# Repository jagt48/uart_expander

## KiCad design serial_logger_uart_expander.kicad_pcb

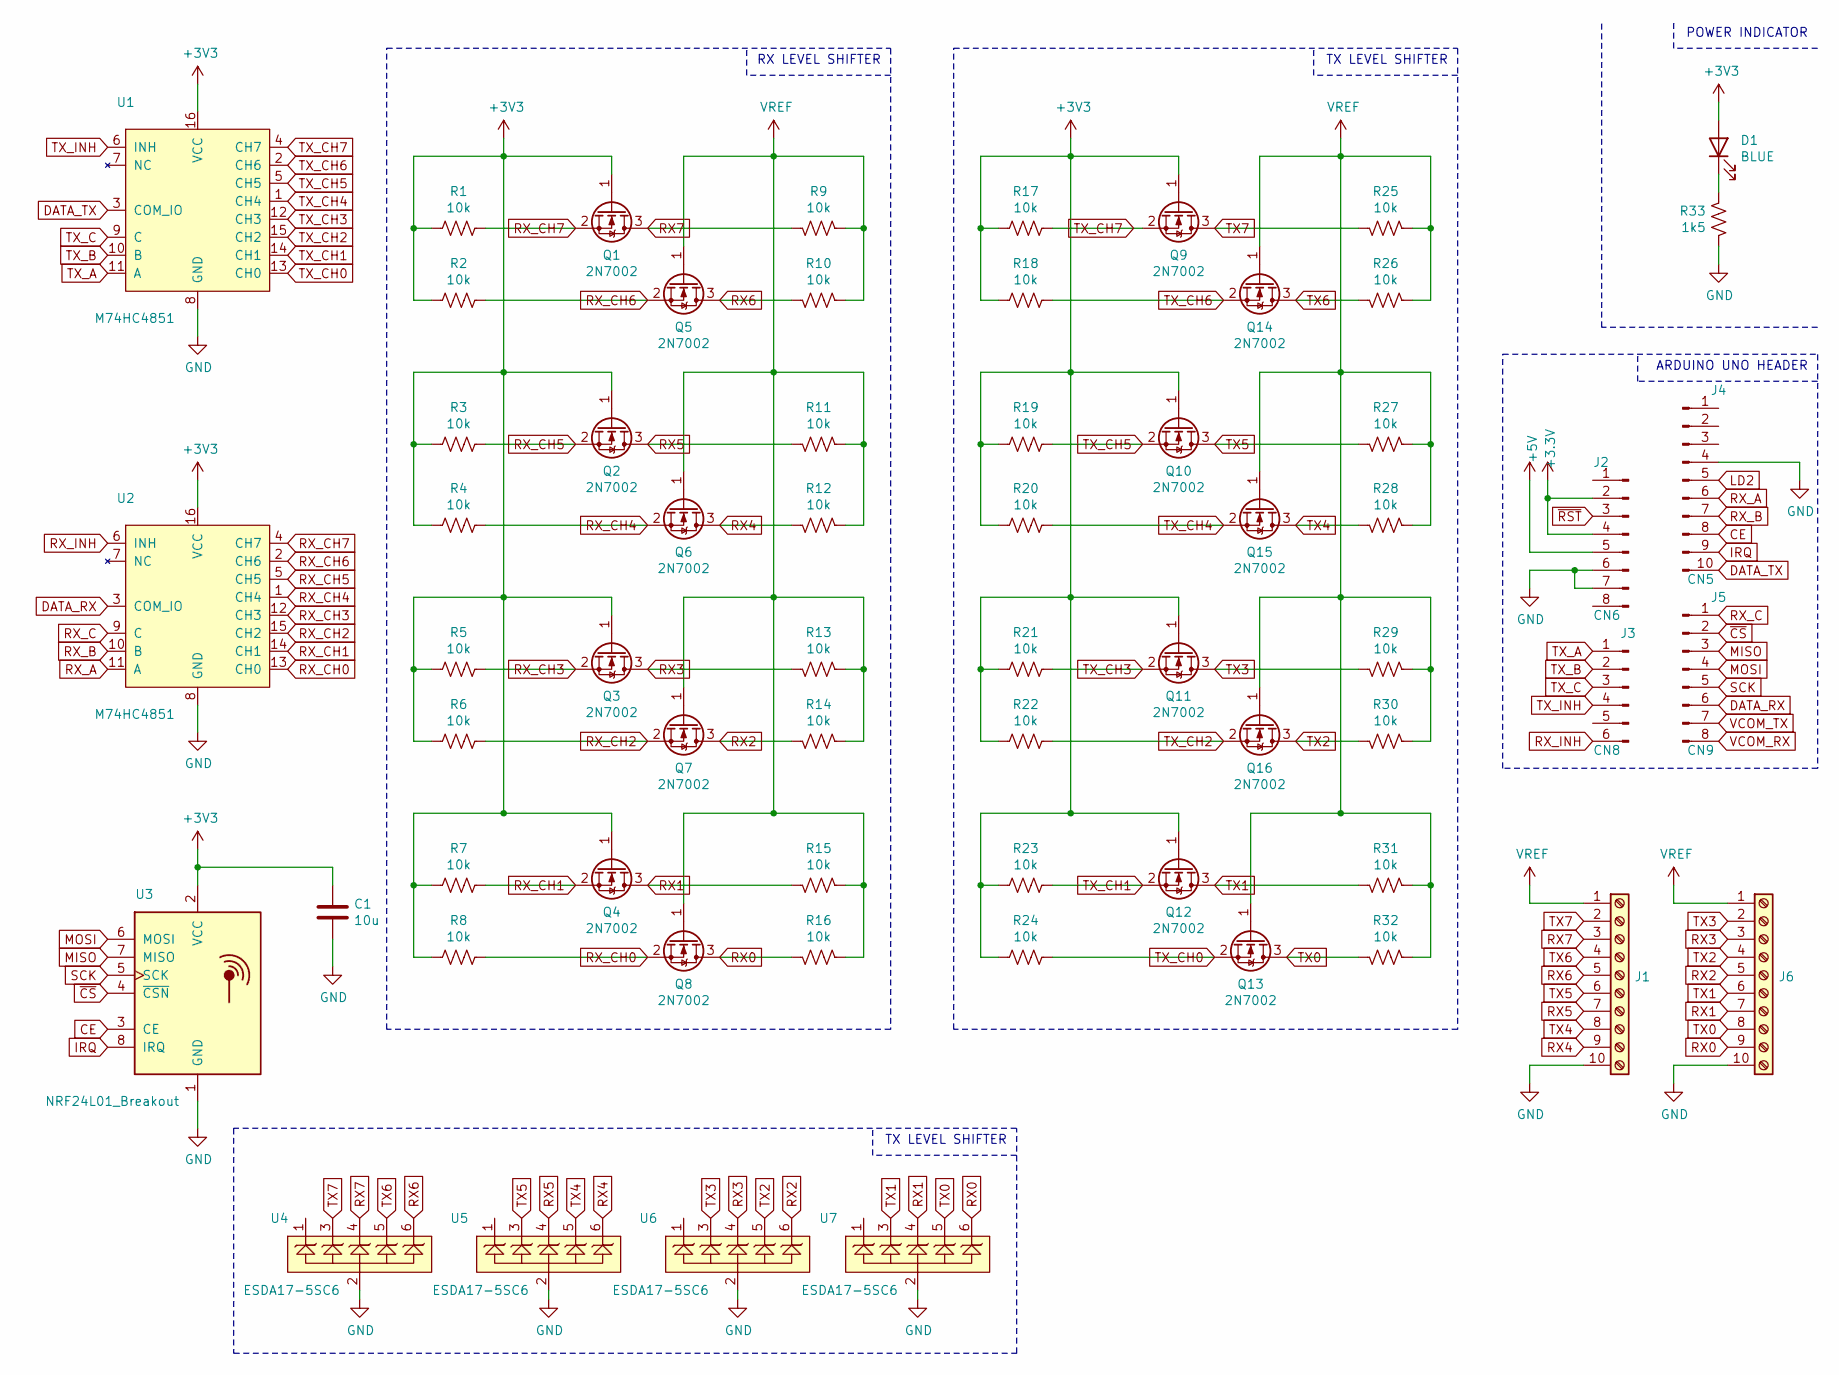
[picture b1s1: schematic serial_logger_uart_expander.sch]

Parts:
C1: 10u; C_0805_2012Metric; LCSC Part # C15850
D1: BLUE; LED_0603_1608Metric_Castellated; LCSC Part # C72041
J1, J6: Screw_Terminal_01x10; TerminalBlock_TE_1-282834-0_1x10_P2.54mm_Horizontal
J2: CN6; PinHeader_1x08_P2.54mm_Vertical
J3: CN8; PinHeader_1x06_P2.54mm_Vertical
J4: CN5; PinHeader_1x10_P2.54mm_Vertical
J5: CN9; PinHeader_1x08_P2.54mm_Vertical
Q1, Q2, Q3, Q4, Q5, Q6, Q7, Q8, Q9, Q10, Q11, Q12, Q13, Q14, Q15, Q16: 2N7002; SOT-23
R1, R2, R3, R4, R5, R6, R7, R8, R9, R10, R11, R12, R13, R14, R15, R16, R17, R18, R19, R20, R21, R22, R23, R24, R25, R26, R27, R28, R29, R30, R31, R32: 10k; R_0603_1608Metric; LCSC Part # C25804
R33: 1k5; R_0603_1608Metric; LCSC Part # C22843
U1, U2: M74HC4851; M74HC4851_ST_TSSOP-16
U3: NRF24L01_Breakout; nRF24L01_Breakout
U4, U5, U6, U7: ESDA17-5SC6; ESDA17-5SC6_SOT23-6L

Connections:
+5V: J2.5
CE: J4.8, U3.3 (CE)
DATA_RX: J5.6, U2.3 (COM_IO)
DATA_TX: J4.10, U1.3 (COM_IO)
GND: C1.2, J1.10, J2.6, J2.7, J4.4, J6.10, R33.1, U1.8 (GND), U2.8 (GND), U3.1 (GND), U4.2, U5.2, U6.2, U7.2
IRQ: J4.9, U3.8 (IRQ)
LD2: J4.5
MISO: J5.3, U3.7 (MISO)
MOSI: J5.4, U3.6 (MOSI)
unnamed: D1.1 (K), R33.2
RX0: J6.9, Q8.3 (D), R16.2, U7.6
RX1: J6.7, Q4.3 (D), R15.2, U7.4
RX2: J6.5, Q7.3 (D), R14.2, U6.6
RX3: J6.3, Q3.3 (D), R13.2, U6.4
RX4: J1.9, Q6.3 (D), R12.2, U5.6
RX5: J1.7, Q2.3 (D), R11.2, U5.4
RX6: J1.5, Q5.3 (D), R10.2, U4.6
RX7: J1.3, Q1.3 (D), R9.2, U4.4
RX_A: J4.6, U2.11 (A)
RX_B: J4.7, U2.10 (B)
RX_C: J5.1, U2.9 (C)
RX_CH0: Q8.2 (S), R8.1, U2.13 (CH0)
RX_CH1: Q4.2 (S), R7.1, U2.14 (CH1)
RX_CH2: Q7.2 (S), R6.1, U2.15 (CH2)
RX_CH3: Q3.2 (S), R5.1, U2.12 (CH3)
RX_CH4: Q6.2 (S), R4.1, U2.1 (CH4)
RX_CH5: Q2.2 (S), R3.1, U2.5 (CH5)
RX_CH6: Q5.2 (S), R2.1, U2.2 (CH6)
RX_CH7: Q1.2 (S), R1.1, U2.4 (CH7)
RX_INH: J3.6, U2.6 (INH)
SCK: J5.5, U3.5 (SCK)
TX0: J6.8, Q13.3 (D), R32.2, U7.5
TX1: J6.6, Q12.3 (D), R31.2, U7.3
TX2: J6.4, Q16.3 (D), R30.2, U6.5
TX3: J6.2, Q11.3 (D), R29.2, U6.3
TX4: J1.8, Q15.3 (D), R28.2, U5.5
TX5: J1.6, Q10.3 (D), R27.2, U5.3
TX6: J1.4, Q14.3 (D), R26.2, U4.5
TX7: J1.2, Q9.3 (D), R25.2, U4.3
TX_A: J3.1, U1.11 (A)
TX_B: J3.2, U1.10 (B)
TX_C: J3.3, U1.9 (C)
TX_CH0: Q13.2 (S), R24.1, U1.13 (CH0)
TX_CH1: Q12.2 (S), R23.1, U1.14 (CH1)
TX_CH2: Q16.2 (S), R22.1, U1.15 (CH2)
TX_CH3: Q11.2 (S), R21.1, U1.12 (CH3)
TX_CH4: Q15.2 (S), R20.1, U1.1 (CH4)
TX_CH5: Q10.2 (S), R19.1, U1.5 (CH5)
TX_CH6: Q14.2 (S), R18.1, U1.2 (CH6)
TX_CH7: Q9.2 (S), R17.1, U1.4 (CH7)
TX_INH: J3.4, U1.6 (INH)
VBUS: J1.1, J6.1, Q5.1 (G), Q6.1 (G), Q7.1 (G), Q8.1 (G), Q13.1 (G), Q14.1 (G), Q15.1 (G), Q16.1 (G), R9.1, R10.1, R11.1, R12.1, R13.1, R14.1, R15.1, R16.1, R25.1, R26.1, R27.1, R28.1, R29.1, R30.1, R31.1, R32.1
VCOM_RX: J5.8
VCOM_TX: J5.7
~CS: J5.2, U3.4 (~CSN)
~RST: J2.3

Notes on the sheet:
POWER INDICATOR
ARDUINO UNO HEADER
TX LEVEL SHIFTER
RX LEVEL SHIFTER

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
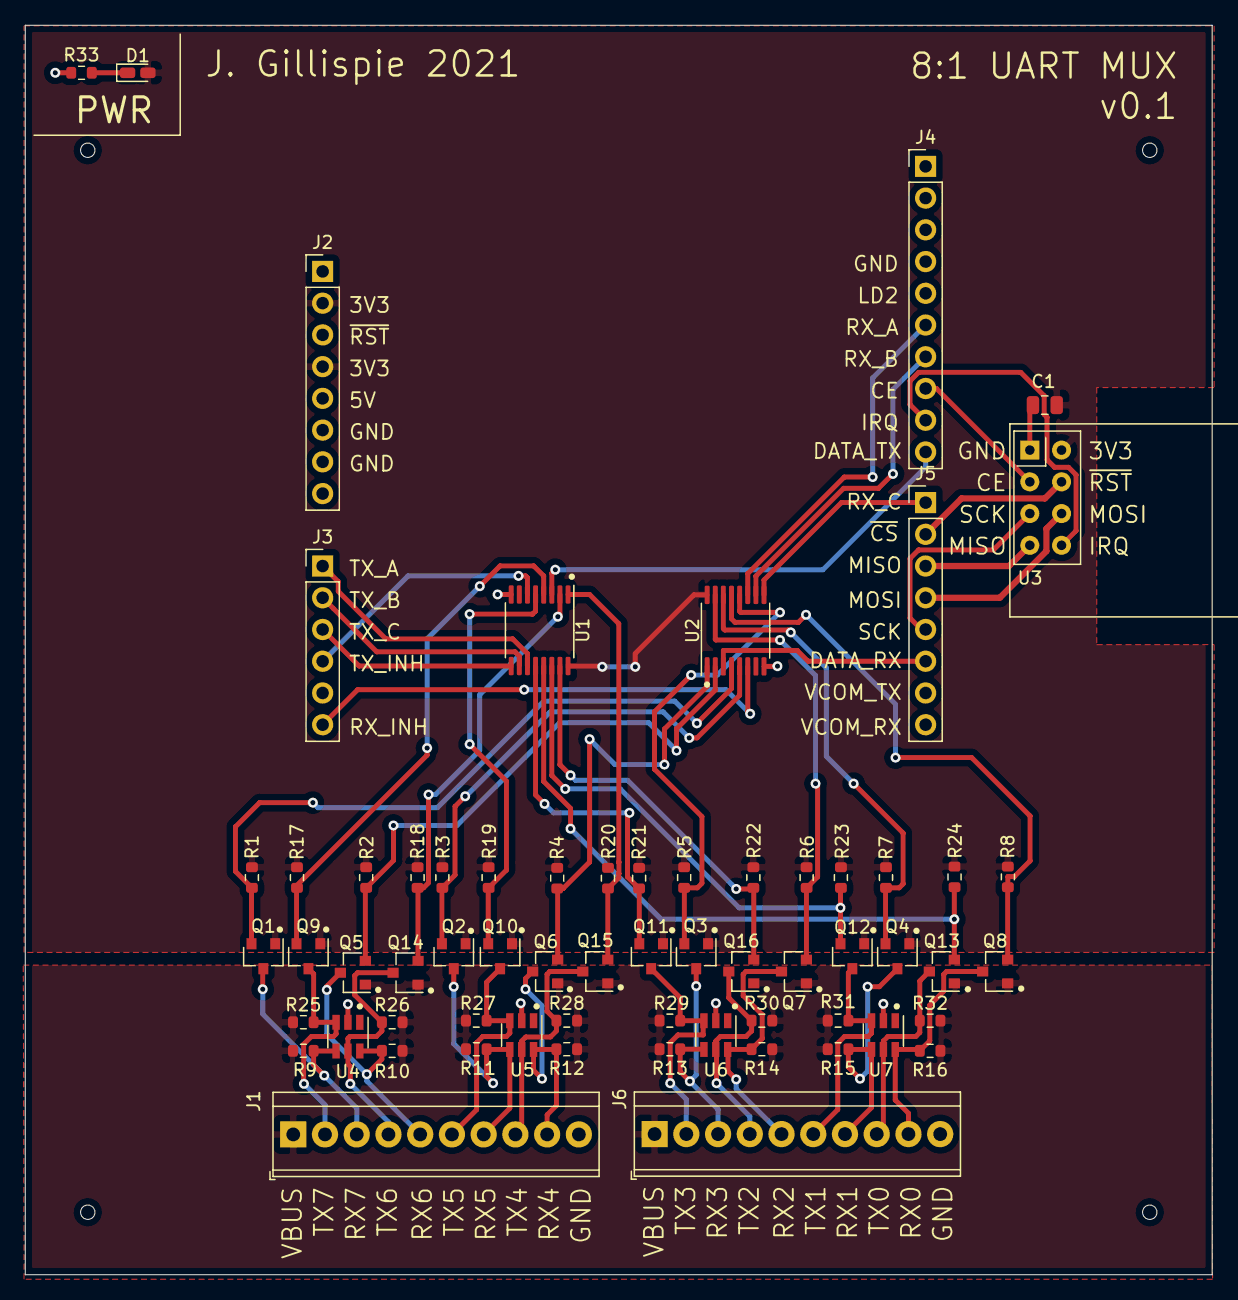
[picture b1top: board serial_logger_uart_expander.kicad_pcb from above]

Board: 2 copper layers, 95.0 x 100.0 mm, 64 parts (0 on the bottom side), 52 nets.

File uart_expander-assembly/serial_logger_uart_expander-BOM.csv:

Designator,Quantity,Value,Footprint,LCSC Part Number
"C1, ",1,10u,0805,C15850
"D1, ",1,BLUE,0603,C72041
"J1, J6, ",2,Screw_Terminal_01x10,TerminalBlock_TE-Connectivity:TerminalBlock_TE_1-282834-0_1x10_P2.54mm_Horizontal,
"J2, ",1,CN6,Connector_PinHeader_2.54mm:PinHeader_1x08_P2.54mm_Vertical,
"J3, ",1,CN8,Connector_PinHeader_2.54mm:PinHeader_1x06_P2.54mm_Vertical,
"J4, ",1,CN5,Connector_PinHeader_2.54mm:PinHeader_1x10_P2.54mm_Vertical,
"J5, ",1,CN9,Connector_PinHeader_2.54mm:PinHeader_1x08_P2.54mm_Vertical,
"Q1, Q2, Q3, Q4, Q5, Q6, Q7, Q8, Q9, Q10, Q11, Q12, Q13, Q14, Q15, Q16, ",16,2N7002,SOT-23-3,C8545
"R1, R2, R3, R4, R5, R6, R7, R8, R9, R10, R11, R12, R13, R14, R15, R16, R17, R18, R19, R20, R21, R22, R23, R24, R25, R26, R27, R28, R29, R30, R31, R32, ",32,10k,0603,C25804 
"R33, ",1,1k5,0603,C22843 
"U1, U2, ",2,M74HC4851,TSSOP-16,
"U3, ",1,NRF24L01_Breakout,RF_Module:nRF24L01_Breakout,
"U4, U5, U6, U7, ",4,ESDA17-5SC6,my_lib:ESDA17-5SC6_SOT23-6L,

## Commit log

2021-09-01 added all libs, sch, and pcb files
2021-09-07 rearranged components and traces
2021-09-14 completed design, no gerbers or BOM.
2021-09-15 v0.0 completed
2021-09-16 started updating mosfets to 2n7002
2021-09-17 completed v0.1 design with 2n7002; no BOM or gerbers
2021-09-17 ordered from jlcpcb on 09/18/2021, order number W202109180255882; possible to use LCSC components for u4..u7
